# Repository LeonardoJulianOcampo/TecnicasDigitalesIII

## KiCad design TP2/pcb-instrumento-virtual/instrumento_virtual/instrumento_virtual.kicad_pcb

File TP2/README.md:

# PCB Para instrumento virtual

## Cosas para hacer

- [ ] Preguntar sobre salidas analógicas (preguntar cuantas son en total)
- [ ] Preguntar sobre tensiones de entradas analógicas

## Cosas para comprar

- [ ] pcb virgen
- [ ] resistencias:
      68K
      33K
      100K
      10k
      
- [ ] Borneras con tornillos x 4 de dos terminales
- [ ] integrados:
      7805
      ams1117-5.0
      operacionales MCP6001 x 8

      DIODOS
- [ ] B0520LW-7-F (diodos shottky)

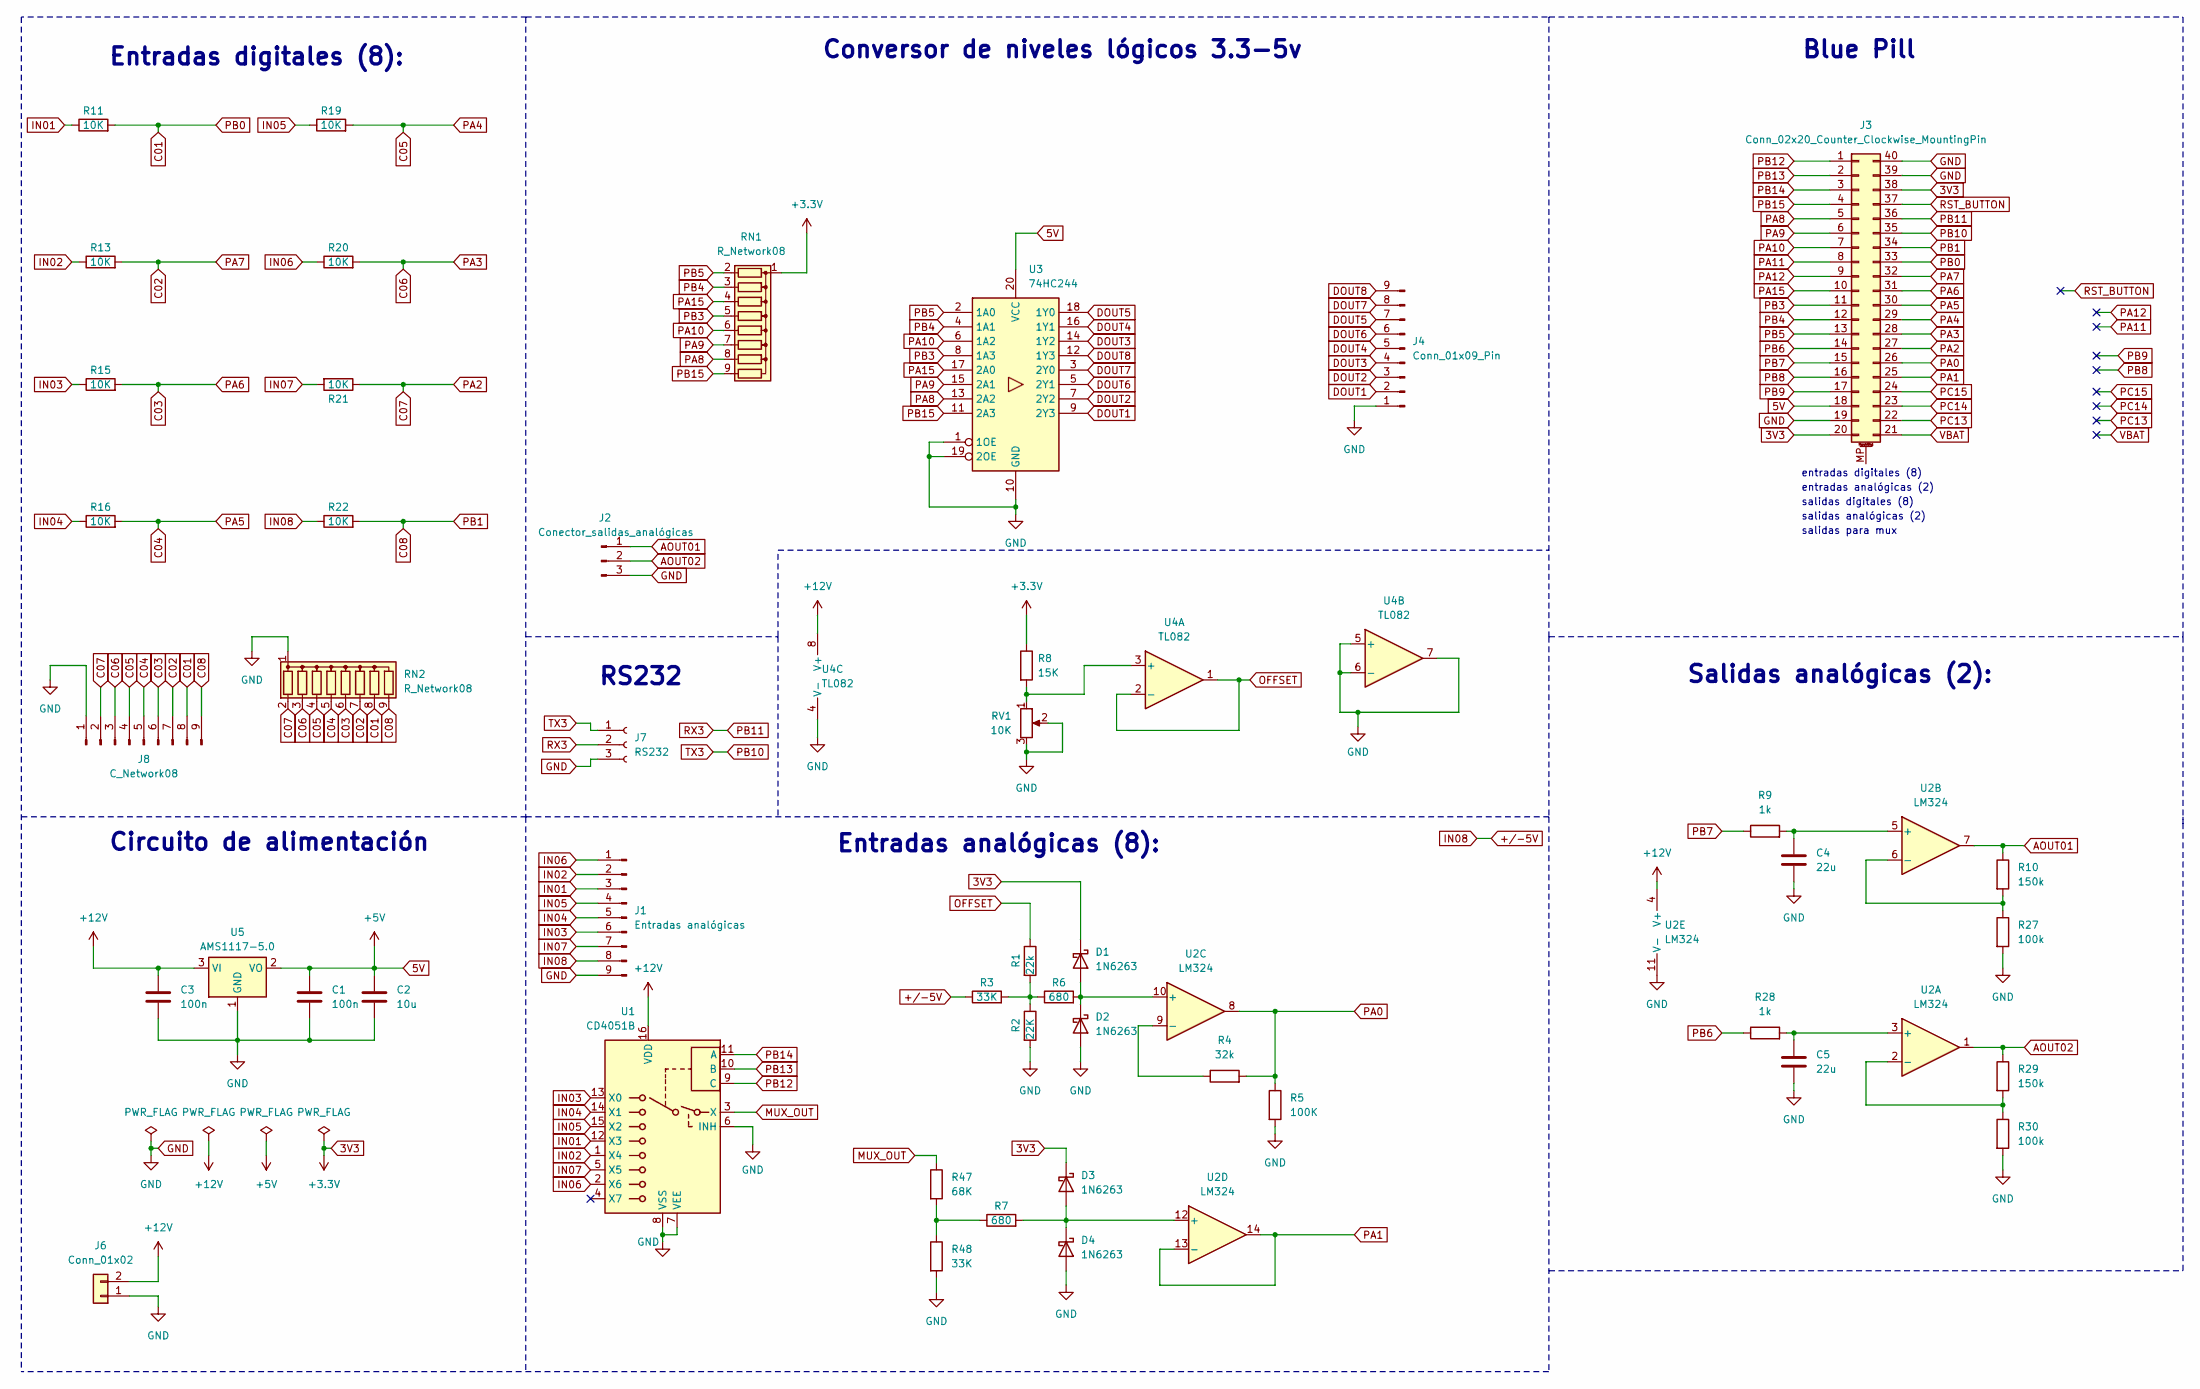
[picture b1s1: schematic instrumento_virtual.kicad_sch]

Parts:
C1, C3: 100n; C_Disc_D9.0mm_W2.5mm_P5.00mm
C2: 10u; CP_Radial_D8.0mm_P5.00mm
C4, C5: 22u; CP_Radial_D8.0mm_P5.00mm
D1, D2, D3, D4: 1N6263; D_DO-35_SOD27_P7.62mm_Horizontal
J1: Entradas analógicas; PinHeader_1x09_P2.54mm_Vertical
J2: Conector_salidas_analógicas; PinHeader_1x03_P2.54mm_Vertical
J3: Conn_02x20_Counter_Clockwise_MountingPin; DIP-40_W15.24mm_LongPads
J4: Conn_01x09_Pin; PinHeader_1x09_P2.54mm_Vertical
J6: Conn_01x02; PinSocket_2x01_P2.54mm_Vertical
J7: RS232; PinHeader_1x03_P2.54mm_Vertical
J8: C_Network08; PinHeader_1x09_P2.54mm_Vertical
R1: 22k; R_Axial_DIN0309_L9.0mm_D3.2mm_P12.70mm_Horizontal
R2: 22K; R_Axial_DIN0309_L9.0mm_D3.2mm_P12.70mm_Horizontal
R3, R48: 33K; R_Axial_DIN0309_L9.0mm_D3.2mm_P12.70mm_Horizontal
R4: 32k; R_Axial_DIN0309_L9.0mm_D3.2mm_P12.70mm_Horizontal
R5: 100K; R_Axial_DIN0309_L9.0mm_D3.2mm_P12.70mm_Horizontal
R6, R7: 680; R_Axial_DIN0309_L9.0mm_D3.2mm_P12.70mm_Horizontal
R8: 15K; R_Axial_DIN0309_L9.0mm_D3.2mm_P12.70mm_Horizontal
R9, R28: 1k; R_Axial_DIN0309_L9.0mm_D3.2mm_P12.70mm_Horizontal
R10, R29: 150k; R_Axial_DIN0309_L9.0mm_D3.2mm_P12.70mm_Horizontal
R11, R13, R15, R16, R19, R20, R21, R22: 10K; R_Axial_DIN0309_L9.0mm_D3.2mm_P12.70mm_Horizontal
R27, R30: 100k; R_Axial_DIN0309_L9.0mm_D3.2mm_P12.70mm_Horizontal
R47: 68K; R_Axial_DIN0309_L9.0mm_D3.2mm_P12.70mm_Horizontal
RN1, RN2: R_Network08; R_Array_SIP9
RV1: 10K; Potentiometer_Bourns_3266Y_Vertical
U1: CD4051B; DIP-16_W7.62mm_LongPads
U2: LM324; DIP-14_W7.62mm
U3: 74HC244; DIP-20_W7.62mm
U4: TL082; DIP-8_W7.62mm
U5: AMS1117-5.0; SOT-223-3_TabPin2

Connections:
3V3: D1.1 (K), D3.1 (K), J3.20, J3.38, R8.1, RN1.1 (common)
5V: C1.1, C2.1, J3.18, U3.20 (VCC), U5.2 (VO)
+12V: C3.1, J6.2, U1.16 (VDD), U2.4 (V+), U4.8 (V+), U5.3 (VI)
+/-5V: J1.8, R3.1, R22.1
AOUT01: J2.1, R10.1, U2.7
AOUT02: J2.2, R29.1, U2.1
C01: J3.33, J8.8, R11.2, RN2.8 (R7)
C02: J3.32, J8.7, R13.2, RN2.7 (R6)
C03: J3.31, J8.6, R15.2, RN2.6 (R5)
C04: J3.30, J8.5, R16.2, RN2.5 (R4)
C05: J3.29, J8.4, R19.2, RN2.4 (R3)
C06: J3.28, J8.3, R20.2, RN2.3 (R2)
C07: J3.27, J8.2, R21.1, RN2.2 (R1)
C08: J3.34, J8.9, R22.2, RN2.9 (R8)
DOUT1: J4.2, U3.9 (2Y3)
DOUT2: J4.3, U3.7 (2Y2)
DOUT3: J4.4, U3.14 (1Y2)
DOUT4: J4.5, U3.16 (1Y1)
DOUT5: J4.7, U3.18 (1Y0)
DOUT6: J4.6, U3.5 (2Y1)
DOUT7: J4.8, U3.3 (2Y0)
DOUT8: J4.9, U3.12 (1Y3)
GND: C1.2, C2.2, C3.2, C4.2, C5.2, D2.2 (A), D4.2 (A), J1.9, J2.3, J3.19, J3.39, J3.40, J4.1, J6.1, J7.3, J8.1, R2.2, R5.2, R27.2, R30.2, R48.2, RN2.1 (common), RV1.2, RV1.3, U1.6 (INH), U1.7 (VEE), U1.8 (VSS), U2.11 (V-), U3.1 (1OE), U3.10 (GND), U3.19 (2OE), U4.4 (V-), U4.5 (+), U4.6 (-), U4.7, U5.1 (GND)
IN01: J1.3, R11.1, U1.12 (X3)
IN02: J1.2, R13.1, U1.1 (X4)
IN03: J1.6, R15.1, U1.13 (X0)
IN04: J1.5, R16.1, U1.14 (X1)
IN05: J1.4, R19.1, U1.15 (X2)
IN06: J1.1, R20.1, U1.2 (X6)
IN07: J1.7, R21.2, U1.5 (X5)
MUX_OUT: R47.1, U1.3 (X)
unnamed: D1.2 (A), D2.1 (K), R6.2, U2.10 (+)
unnamed: D3.2 (A), D4.1 (K), R7.2, U2.12 (+)
unnamed: R1.2, R2.1, R3.2, R6.1
unnamed: R7.1, R47.2, R48.1
unnamed: C5.1, R28.2, U2.3 (+)
unnamed: R29.2, R30.1, U2.2 (-)
unnamed: C4.1, R9.2, U2.5 (+)
unnamed: R10.2, R27.1, U2.6 (-)
unnamed: R4.1, U2.9 (-)
unnamed: R8.2, RV1.1, U4.3 (+)
OFFSET: R1.1, U4.1, U4.2 (-)
PA0: J3.26, R4.2, R5.1, U2.8
PA1: J3.25, U2.13 (-), U2.14
PA8: J3.5, RN1.8 (R7), U3.13 (2A2)
PA9: J3.6, RN1.7 (R6), U3.15 (2A1)
PA10: J3.7, RN1.6 (R5), U3.6 (1A2)
PA11: J3.8
PA12: J3.9
PA15: J3.10, RN1.4 (R3), U3.17 (2A0)
PB3: J3.11, RN1.5 (R4), U3.8 (1A3)
PB4: J3.12, RN1.3 (R2), U3.4 (1A1)
PB5: J3.13, RN1.2 (R1), U3.2 (1A0)
PB6: J3.14, R28.1
PB7: J3.15, R9.1
PB8: J3.16
PB9: J3.17
PB10: J3.35, J7.1
PB11: J3.36, J7.2
PB12: J3.1, U1.9 (C)
PB13: J3.2, U1.10 (B)
PB14: J3.3, U1.11 (A)
PB15: J3.4, RN1.9 (R8), U3.11 (2A3)
PC13: J3.22
PC14: J3.23
PC15: J3.24
RST_BUTTON: J3.37
VBAT: J3.21

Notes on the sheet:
entradas digitales (8)
entradas analógicas (2)
Entradas analógicas (8):
Entradas digitales (8):
Conversor de niveles lógicos 3.3-5v
salidas digitales (8)
salidas para mux
Blue Pill
RS232
Circuito de alimentación
salidas analógicas (2)
Salidas analógicas (2):

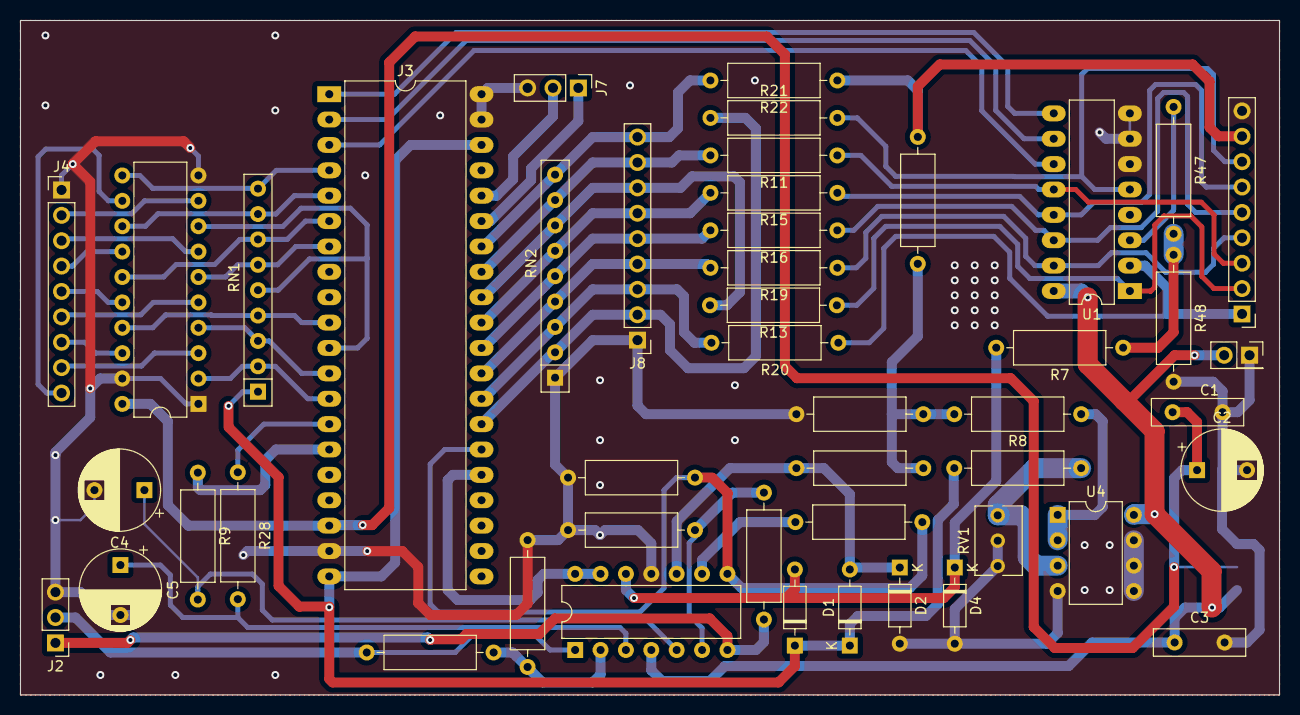
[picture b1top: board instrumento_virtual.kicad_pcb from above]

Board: 2 copper layers, 126.0 x 67.5 mm, 48 parts (1 on the bottom side), 59 nets.

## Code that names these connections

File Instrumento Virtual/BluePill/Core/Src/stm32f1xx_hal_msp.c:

/* USER CODE BEGIN Header */
/**
  ******************************************************************************
  * @file         stm32f1xx_hal_msp.c
  * @brief        This file provides code for the MSP Initialization
  *               and de-Initialization codes.
  ******************************************************************************
  * @attention
  *
  * Copyright (c) 2023 STMicroelectronics.
  * All rights reserved.
  *
  * This software is licensed under terms that can be found in the LICENSE file
  * in the root directory of this software component.
  * If no LICENSE file comes with this software, it is provided AS-IS.
  *
  ******************************************************************************
  */
/* USER CODE END Header */

/* Includes ------------------------------------------------------------------*/
#include "main.h"

/* USER CODE BEGIN Includes */

/* USER CODE END Includes */

/* Private typedef -----------------------------------------------------------*/
/* USER CODE BEGIN TD */

/* USER CODE END TD */

/* Private define ------------------------------------------------------------*/
/* USER CODE BEGIN Define */

/* USER CODE END Define */

/* Private macro -------------------------------------------------------------*/
/* USER CODE BEGIN Macro */

/* USER CODE END Macro */

/* Private variables ---------------------------------------------------------*/
/* USER CODE BEGIN PV */

/* USER CODE END PV */

/* Private function prototypes -----------------------------------------------*/
/* USER CODE BEGIN PFP */

/* USER CODE END PFP */

/* External functions --------------------------------------------------------*/
/* USER CODE BEGIN ExternalFunctions */

/* USER CODE END ExternalFunctions */

/* USER CODE BEGIN 0 */

/* USER CODE END 0 */

void HAL_TIM_MspPostInit(TIM_HandleTypeDef *htim);
                    /**
  * Initializes the Global MSP.
  */
void HAL_MspInit(void)
{
  /* USER CODE BEGIN MspInit 0 */

  /* USER CODE END MspInit 0 */

  __HAL_RCC_AFIO_CLK_ENABLE();
  __HAL_RCC_PWR_CLK_ENABLE();

  /* System interrupt init*/

  /** NOJTAG: JTAG-DP Disabled and SW-DP Enabled
  */
  __HAL_AFIO_REMAP_SWJ_NOJTAG();

  /* USER CODE BEGIN MspInit 1 */

  /* USER CODE END MspInit 1 */
}

/**
* @brief ADC MSP Initialization
* This function configures the hardware resources used in this example
* @param hadc: ADC handle pointer
* @retval None
*/
void HAL_ADC_MspInit(ADC_HandleTypeDef* hadc)
{
  GPIO_InitTypeDef GPIO_InitStruct = {0};
  if(hadc->Instance==ADC1)
  {
  /* USER CODE BEGIN ADC1_MspInit 0 */

  /* USER CODE END ADC1_MspInit 0 */
    /* Peripheral clock enable */
    __HAL_RCC_ADC1_CLK_ENABLE();

    __HAL_RCC_GPIOA_CLK_ENABLE();
    /**ADC1 GPIO Configuration
    PA0-WKUP     ------> ADC1_IN0
    PA1     ------> ADC1_IN1
    */
    GPIO_InitStruct.Pin = A_IN8_Pin|IN_MUX_Pin;
    GPIO_InitStruct.Mode = GPIO_MODE_ANALOG;
    HAL_GPIO_Init(GPIOA, &GPIO_InitStruct);

    /* ADC1 interrupt Init */
    HAL_NVIC_SetPriority(ADC1_2_IRQn, 0, 0);
    HAL_NVIC_EnableIRQ(ADC1_2_IRQn);
  /* USER CODE BEGIN ADC1_MspInit 1 */

  /* USER CODE END ADC1_MspInit 1 */
  }

}

/**
* @brief ADC MSP De-Initialization
* This function freeze the hardware resources used in this example
* @param hadc: ADC handle pointer
* @retval None
*/
void HAL_ADC_MspDeInit(ADC_HandleTypeDef* hadc)
{
  if(hadc->Instance==ADC1)
  {
  /* USER CODE BEGIN ADC1_MspDeInit 0 */

  /* USER CODE END ADC1_MspDeInit 0 */
    /* Peripheral clock disable */
    __HAL_RCC_ADC1_CLK_DISABLE();

    /**ADC1 GPIO Configuration
    PA0-WKUP     ------> ADC1_IN0
    PA1     ------> ADC1_IN1
    */
    HAL_GPIO_DeInit(GPIOA, A_IN8_Pin|IN_MUX_Pin);

    /* ADC1 interrupt DeInit */
    HAL_NVIC_DisableIRQ(ADC1_2_IRQn);
  /* USER CODE BEGIN ADC1_MspDeInit 1 */

  /* USER CODE END ADC1_MspDeInit 1 */
  }

}

/**
* @brief TIM_Base MSP Initialization
* This function configures the hardware resources used in this example
* @param htim_base: TIM_Base handle pointer
* @retval None
*/
void HAL_TIM_Base_MspInit(TIM_HandleTypeDef* htim_base)
{
  if(htim_base->Instance==TIM1)
  {
  /* USER CODE BEGIN TIM1_MspInit 0 */

  /* USER CODE END TIM1_MspInit 0 */
    /* Peripheral clock enable */
    __HAL_RCC_TIM1_CLK_ENABLE();
    /* TIM1 interrupt Init */
    HAL_NVIC_SetPriority(TIM1_UP_IRQn, 0, 0);
    HAL_NVIC_EnableIRQ(TIM1_UP_IRQn);
  /* USER CODE BEGIN TIM1_MspInit 1 */

  /* USER CODE END TIM1_MspInit 1 */
  }
  else if(htim_base->Instance==TIM4)
  {
  /* USER CODE BEGIN TIM4_MspInit 0 */

  /* USER CODE END TIM4_MspInit 0 */
    /* Peripheral clock enable */
    __HAL_RCC_TIM4_CLK_ENABLE();
  /* USER CODE BEGIN TIM4_MspInit 1 */

  /* USER CODE END TIM4_MspInit 1 */
  }

}

void HAL_TIM_MspPostInit(TIM_HandleTypeDef* htim)
{
  GPIO_InitTypeDef GPIO_InitStruct = {0};
  if(htim->Instance==TIM4)
  {
  /* USER CODE BEGIN TIM4_MspPostInit 0 */

  /* USER CODE END TIM4_MspPostInit 0 */

    __HAL_RCC_GPIOB_CLK_ENABLE();
    /**TIM4 GPIO Configuration
    PB6     ------> TIM4_CH1
    PB7     ------> TIM4_CH2
    */
    GPIO_InitStruct.Pin = A_OUT2_Pin|A_OUT1_Pin;
    GPIO_InitStruct.Mode = GPIO_MODE_AF_PP;
    GPIO_InitStruct.Speed = GPIO_SPEED_FREQ_LOW;
    HAL_GPIO_Init(GPIOB, &GPIO_InitStruct);

  /* USER CODE BEGIN TIM4_MspPostInit 1 */

  /* USER CODE END TIM4_MspPostInit 1 */
  }

}
/**
* @brief TIM_Base MSP De-Initialization
* This function freeze the hardware resources used in this example
* @param htim_base: TIM_Base handle pointer
* @retval None
*/
void HAL_TIM_Base_MspDeInit(TIM_HandleTypeDef* htim_base)
{
  if(htim_base->Instance==TIM1)
  {
  /* USER CODE BEGIN TIM1_MspDeInit 0 */

  /* USER CODE END TIM1_MspDeInit 0 */
    /* Peripheral clock disable */
    __HAL_RCC_TIM1_CLK_DISABLE();

    /* TIM1 interrupt DeInit */
    HAL_NVIC_DisableIRQ(TIM1_UP_IRQn);
  /* USER CODE BEGIN TIM1_MspDeInit 1 */

  /* USER CODE END TIM1_MspDeInit 1 */
  }
  else if(htim_base->Instance==TIM4)
  {
  /* USER CODE BEGIN TIM4_MspDeInit 0 */

  /* USER CODE END TIM4_MspDeInit 0 */
    /* Peripheral clock disable */
    __HAL_RCC_TIM4_CLK_DISABLE();
  /* USER CODE BEGIN TIM4_MspDeInit 1 */

  /* USER CODE END TIM4_MspDeInit 1 */
  }

}

/**
* @brief UART MSP Initialization
* This function configures the hardware resources used in this example
* @param huart: UART handle pointer
* @retval None
*/
void HAL_UART_MspInit(UART_HandleTypeDef* huart)
{
  GPIO_InitTypeDef GPIO_InitStruct = {0};
  if(huart->Instance==USART3)
  {
  /* USER CODE BEGIN USART3_MspInit 0 */

  /* USER CODE END USART3_MspInit 0 */
    /* Peripheral clock enable */
    __HAL_RCC_USART3_CLK_ENABLE();

    __HAL_RCC_GPIOB_CLK_ENABLE();
    /**USART3 GPIO Configuration
    PB10     ------> USART3_TX
    PB11     ------> USART3_RX
    */
    GPIO_InitStruct.Pin = GPIO_PIN_10;
    GPIO_InitStruct.Mode = GPIO_MODE_AF_PP;
    GPIO_InitStruct.Speed = GPIO_SPEED_FREQ_HIGH;
    HAL_GPIO_Init(GPIOB, &GPIO_InitStruct);

    GPIO_InitStruct.Pin = GPIO_PIN_11;
    GPIO_InitStruct.Mode = GPIO_MODE_INPUT;
    GPIO_InitStruct.Pull = GPIO_NOPULL;
    HAL_GPIO_Init(GPIOB, &GPIO_InitStruct);

    /* USART3 interrupt Init */
    HAL_NVIC_SetPriority(USART3_IRQn, 0, 0);
    HAL_NVIC_EnableIRQ(USART3_IRQn);
  /* USER CODE BEGIN USART3_MspInit 1 */

  /* USER CODE END USART3_MspInit 1 */
  }

}

/**
* @brief UART MSP De-Initialization
* This function freeze the hardware resources used in this example
* @param huart: UART handle pointer
* @retval None
*/
void HAL_UART_MspDeInit(UART_HandleTypeDef* huart)
{
  if(huart->Instance==USART3)
  {
  /* USER CODE BEGIN USART3_MspDeInit 0 */

  /* USER CODE END USART3_MspDeInit 0 */
    /* Peripheral clock disable */
    __HAL_RCC_USART3_CLK_DISABLE();

    /**USART3 GPIO Configuration
    PB10     ------> USART3_TX
    PB11     ------> USART3_RX
    */
    HAL_GPIO_DeInit(GPIOB, GPIO_PIN_10|GPIO_PIN_11);

    /* USART3 interrupt DeInit */
    HAL_NVIC_DisableIRQ(USART3_IRQn);
  /* USER CODE BEGIN USART3_MspDeInit 1 */

  /* USER CODE END USART3_MspDeInit 1 */
  }

}

/* USER CODE BEGIN 1 */

/* USER CODE END 1 */

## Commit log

2023-07-25 Agregue carpeta TP3
2023-07-26 agrega consigna tp3
2023-07-27 primer qt
2023-07-27 archivo 1
2023-07-28 serial-port
2023-08-17 Modifica nombre de la carpeta por TP3 para mejor organización
2023-08-17 agrega rama alternativo que contiene el tp2 funcionando
2023-08-17 archivo binario funcionando
2023-08-28 error del while solucionado
2023-08-28 binario final
2023-09-24 crea proyecto de pcb para instrumento virtual
2023-09-24 añade readme
2023-09-24 Update README.md
    Añadida lista de compras
2023-09-24 agrega etapas de operacionales de entradas y circuitos de protección con clamping diodes en la pcb
2023-09-25 añade simulación de clamping diodes para protección de las entradas analógicas
2023-10-07 modifca pcb
2023-10-14 Version de pcb con regulación de 5v
2023-10-16 primera versión tentativa de esquemático
2023-10-17 cambiado circuito de adaptacion de niveles logicos
2023-10-24 pcb actualizada
2023-10-25 version final pcb
2023-10-27 version inicial para programa QT
2023-11-19 Se agrega codigo de la bluepill
2023-11-19 Se agregan las configuraciones del pwm y algunas modificaciones generales
2023-11-19 Se corrigen errores de compilacion
2023-11-20 Se agrega la interface de QT, falta unir con la vieja interface
2023-11-20 Se modifica frecuencia del timer 4 que maneja el PWM a 6HZ
2023-11-24 Salidas y entradas virtuales del instrumento virtual andando
2023-11-27 corrige mapeo de pines de selección de mux y errores de tipeos
